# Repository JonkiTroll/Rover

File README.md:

# Rover
Implementation of a rc tank. Based on rctestflight's design.

# Requirements
Python 3.8 on server and rover

pyttsx3 python library for RoverTTS.py. For Ubuntu linux, libespeak1 needs to be installed manually (sudo apt install libespeak1).

OpenCv2 for Video_server.py. 

# Utilities
GPS 	GY-NEO6MV2

IMU	Icm20948 (Pid controller)

Camera (Servo)  logitech webcam

Speakers

Temp, gas, barometer, humidity https://www.bosch-sensortec.com/products/environmental-sensors/gas-sensors/bme688/

Neopixels

Battery management (Fuel gauge) https://www.ti.com/product/BQ34110#product-details##description

expansion headers (Servos, analog pins)

Hall Effect sensors x2 (3390Q)

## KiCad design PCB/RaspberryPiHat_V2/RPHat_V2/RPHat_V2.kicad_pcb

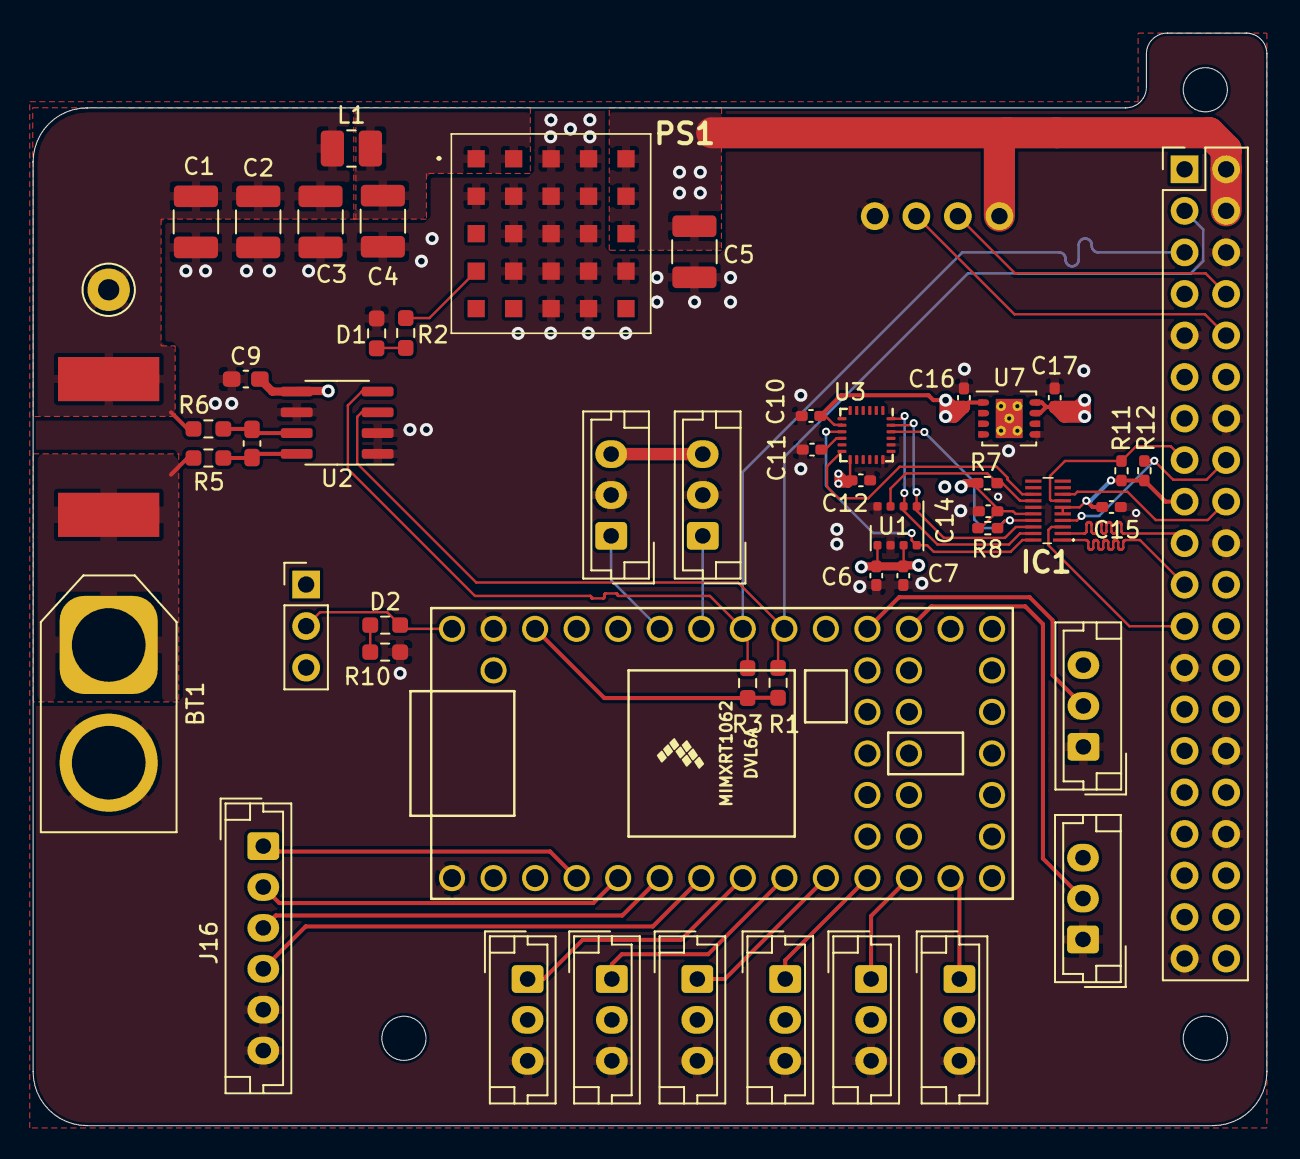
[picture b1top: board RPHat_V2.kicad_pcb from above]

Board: 4 copper layers, 75.4 x 66.8 mm, 53 parts (0 on the bottom side), 44 nets.

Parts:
BT1: Battery; AMASS_XT60-M_1x02_P7.20mm_Vertical
C1, C2, C3, C4, C5: 10uF; C_1210_3225Metric_Pad1.33x2.70mm_HandSolder
C6, C7, C10, C11, C12, C14, C15: 100nF; C_0402_1005Metric_Pad0.74x0.62mm_HandSolder
C8: DNC; C_0603_1608Metric_Pad1.08x0.95mm_HandSolder
C9: 100nF; C_0603_1608Metric_Pad1.08x0.95mm_HandSolder
C16: 4,7uF; C_0402_1005Metric_Pad0.74x0.62mm_HandSolder
C17: 1uF; C_0402_1005Metric_Pad0.74x0.62mm_HandSolder
D1, D2: LED; R_0603_1608Metric_Pad0.98x0.95mm_HandSolder
IC1: TXB0108DQSR
J1: Raspberry_Pi_2_3; PinHeader_2x20_P2.54mm_Vertical
J2: Hall effect connector Right; JST_EH_B3B-EH-A_1x03_P2.50mm_Vertical
J3: Halleffect Connector Left; JST_EH_B3B-EH-A_1x03_P2.50mm_Vertical
J5, J6, J7, J8, J11, J12, J13, J14: Conn_01x03; JST_EH_B3B-EH-A_1x03_P2.50mm_Vertical
J15: Conn_01x01; Pin_D1.3mm_L11.0mm
J16: Conn_01x06; JST_EH_B6B-EH-A_1x06_P2.50mm_Vertical
L1: 2.2uH; L_1008_2520Metric_Pad1.43x2.20mm_HandSolder
PS1: RPMB5.0-3.0; RPMB5030
R1, R3: TBU; R_0603_1608Metric_Pad0.98x0.95mm_HandSolder
R2: 1k; R_0603_1608Metric_Pad0.98x0.95mm_HandSolder
R4: 0.05; CSS2H-3920
R5, R6: 0; R_0603_1608Metric_Pad0.98x0.95mm_HandSolder
R7, R8, R11, R12: 100k; R_0402_1005Metric_Pad0.72x0.64mm_HandSolder
R10: 4.7k; R_0603_1608Metric_Pad0.98x0.95mm_HandSolder
SW1: SW_DPDT_x2; PinHeader_1x03_P2.54mm_Vertical
U1: BME680; Bosch_LGA-8_3x3mm_P0.8mm_ClockwisePinNumbering
U2: INA219AxD; SOIC-8_3.9x4.9mm_P1.27mm
U3: ICM-20948; InvenSense_QFN-24_3x3mm_P0.4mm
U4: GY-NEO6MV2
U6: Teensy4.0; Teensy40
U7: TPS78418QWDRBRQ1; Texas_S-PVSON-N8_ThermalVias

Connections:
+1V8: C6.1, C7.1, C10.1, C12.1, C14.1, C16.1, IC1.16, R7.1, R8.1, U1.6, U1.8, U3.8, U3.13, U7.1
+3V3: C9.1, C15.1, C17.1, IC1.5, IC1.6, J1.1, J1.17, J2.3, J3.3, R1.1, R3.1, R11.1, R12.1, U2.5, U6.31, U7.7, U7.8
+5V: C5.1, J1.2, J1.4, J5.2, J6.2, J7.2, J8.2, J11.3, J12.3, J13.2, J14.2, PS1.A5, PS1.B5, PS1.C5, SW1.1, U4.4
+BATT: BT1.1, R4.2, R5.1
BME_CS_18: IC1.14, R7.2, U1.2
BME_CS_33: IC1.7, J1.15, R11.2
GNDREF: BT1.2, C1.2, C2.2, C3.2, C4.2, C5.2, C6.2, C7.2, C9.2, C10.2, C11.2, C12.2, C14.2, C15.2, C16.2, C17.2, D1.1, IC1.15, J1.6, J1.9, J1.14, J1.20, J1.25, J1.30, J1.34, J1.39, J2.2, J3.2, J5.3, J6.3, J7.3, J8.3, J11.1, J12.1, J13.3, J14.3, J16.5, J16.6, PS1.A3, PS1.A4, PS1.B1, PS1.B2, PS1.B3, PS1.B4, PS1.C2, PS1.C3, PS1.C4, PS1.D2, PS1.D3, PS1.D4, PS1.D5, PS1.E3, PS1.E4, R10.2, U1.1, U1.7, U2.1, U2.2, U2.6, U3.18, U3.20, U4.1, U6.1, U6.32, U7.5, U7.9
GPS_RX: J1.8, U4.3
GPS_TX: J1.10, U4.2
HE_L_OUTPUT: J3.1, U6.28
HE_R_OUTPUT: J2.1, U6.27
IMU_CS_18: IC1.17, R8.2, U3.22
IMU_CS_33: IC1.4, J1.16, R12.2
IMU_INT_18: IC1.13, U3.12
IMU_INT_33: IC1.8, J1.18
Neopixels_1: J11.2, U6.22
Neopixels_2: J12.2, U6.23
unnamed: C4.1, L1.2, PS1.A1, PS1.A2
unnamed: C8.1, R5.2, U2.8
unnamed: C8.2, R6.2, U2.7
unnamed: C11.1, U3.10
unnamed: D1.2, R2.2
unnamed: D2.1, R10.1
unnamed: D2.2, SW1.2, U6.33
unnamed: PS1.D1, R2.1
PWM_Left_1: J16.2, U6.5
PWM_Left_2: J16.4, U6.7
PWM_Right_1: J16.1, U6.4
PWM_Right_2: J16.3, U6.6
PWMservo_1: J5.1, U6.8
PWMservo_2: J6.1, U6.9
PWMservo_3: J7.1, U6.10
PWMservo_4: J8.1, U6.11
PWMservo_5: J13.1, U6.12
PWMservo_6: J14.1, U6.13
SCL: J1.5, R3.2, U2.4, U6.26
SDA: J1.3, R1.2, U2.3, U6.25
SPI_CLK_18: IC1.18, U1.4, U3.23
SPI_CLK_33: IC1.3, J1.23
SPI_MISO_18: IC1.20, U1.5, U3.9
SPI_MISO_33: IC1.1, J1.21
SPI_MOSI_18: IC1.19, U1.3, U3.24
SPI_MOSI_33: IC1.2, J1.19
VCC: C1.1, C2.1, C3.1, J15.1, L1.1, R4.1, R6.1

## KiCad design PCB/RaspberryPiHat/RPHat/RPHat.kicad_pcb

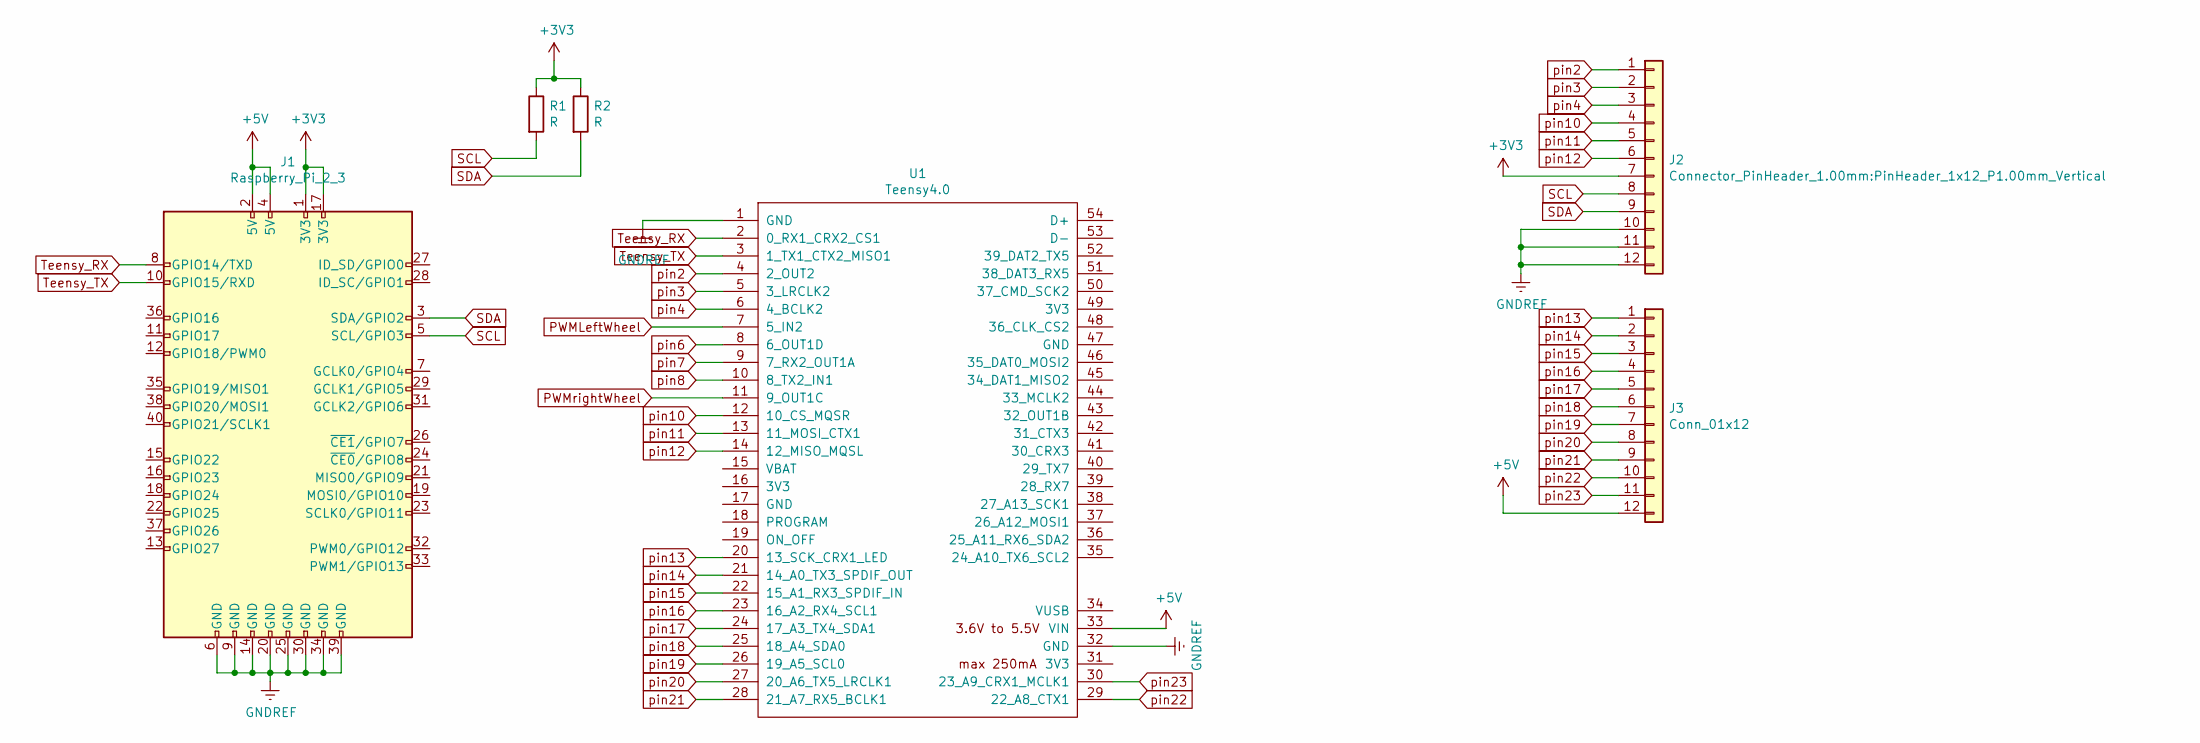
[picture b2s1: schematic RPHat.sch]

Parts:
J1: Raspberry_Pi_2_3; PinSocket_2x20_P2.54mm_Vertical
J2: Connector_PinHeader_1.00mm:PinHeader_1x12_P1.00mm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; PinHeader_1x12_P2.54mm_Vertical
J3: Conn_01x12; PinHeader_1x12_P2.54mm_Vertical
R1, R2: R; R_Box_L13.0mm_W4.0mm_P9.00mm
U1: Teensy4.0; Teensy40

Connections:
+3V3: J1.1 (3V3), J1.17 (3V3), J2.7, R1.1, R2.1
+5V: J1.2 (5V), J1.4 (5V), J3.12, U1.33 (VIN)
GNDREF: J1.6 (GND), J1.9 (GND), J1.14 (GND), J1.20 (GND), J1.25 (GND), J1.30 (GND), J1.34 (GND), J1.39 (GND), J2.10, J2.11, J2.12, U1.1 (GND), U1.32 (GND)
PWMLeftWheel: U1.7 (5_IN2)
PWMrightWheel: U1.11 (9_OUT1C)
SCL: J1.5 (SCL/GPIO3), J2.8, R1.2
SDA: J1.3 (SDA/GPIO2), J2.9, R2.2
Teensy_RX: J1.8 (GPIO14/TXD), U1.2 (0_RX1_CRX2_CS1)
Teensy_TX: J1.10 (GPIO15/RXD), U1.3 (1_TX1_CTX2_MISO1)
pin2: J2.1, U1.4 (2_OUT2)
pin3: J2.2, U1.5 (3_LRCLK2)
pin4: J2.3, U1.6 (4_BCLK2)
pin6: U1.8 (6_OUT1D)
pin7: U1.9 (7_RX2_OUT1A)
pin8: U1.10 (8_TX2_IN1)
pin10: J2.4, U1.12 (10_CS_MQSR)
pin11: J2.5, U1.13 (11_MOSI_CTX1)
pin12: J2.6, U1.14 (12_MISO_MQSL)
pin13: J3.1, U1.20 (13_SCK_CRX1_LED)
pin14: J3.2, U1.21 (14_A0_TX3_SPDIF_OUT)
pin15: J3.3, U1.22 (15_A1_RX3_SPDIF_IN)
pin16: J3.4, U1.23 (16_A2_RX4_SCL1)
pin17: J3.5, U1.24 (17_A3_TX4_SDA1)
pin18: J3.6, U1.25 (18_A4_SDA0)
pin19: J3.7, U1.26 (19_A5_SCL0)
pin20: J3.8, U1.27 (20_A6_TX5_LRCLK1)
pin21: J3.9, U1.28 (21_A7_RX5_BCLK1)
pin22: J3.10, U1.29 (22_A8_CTX1)
pin23: J3.11, U1.30 (23_A9_CRX1_MCLK1)

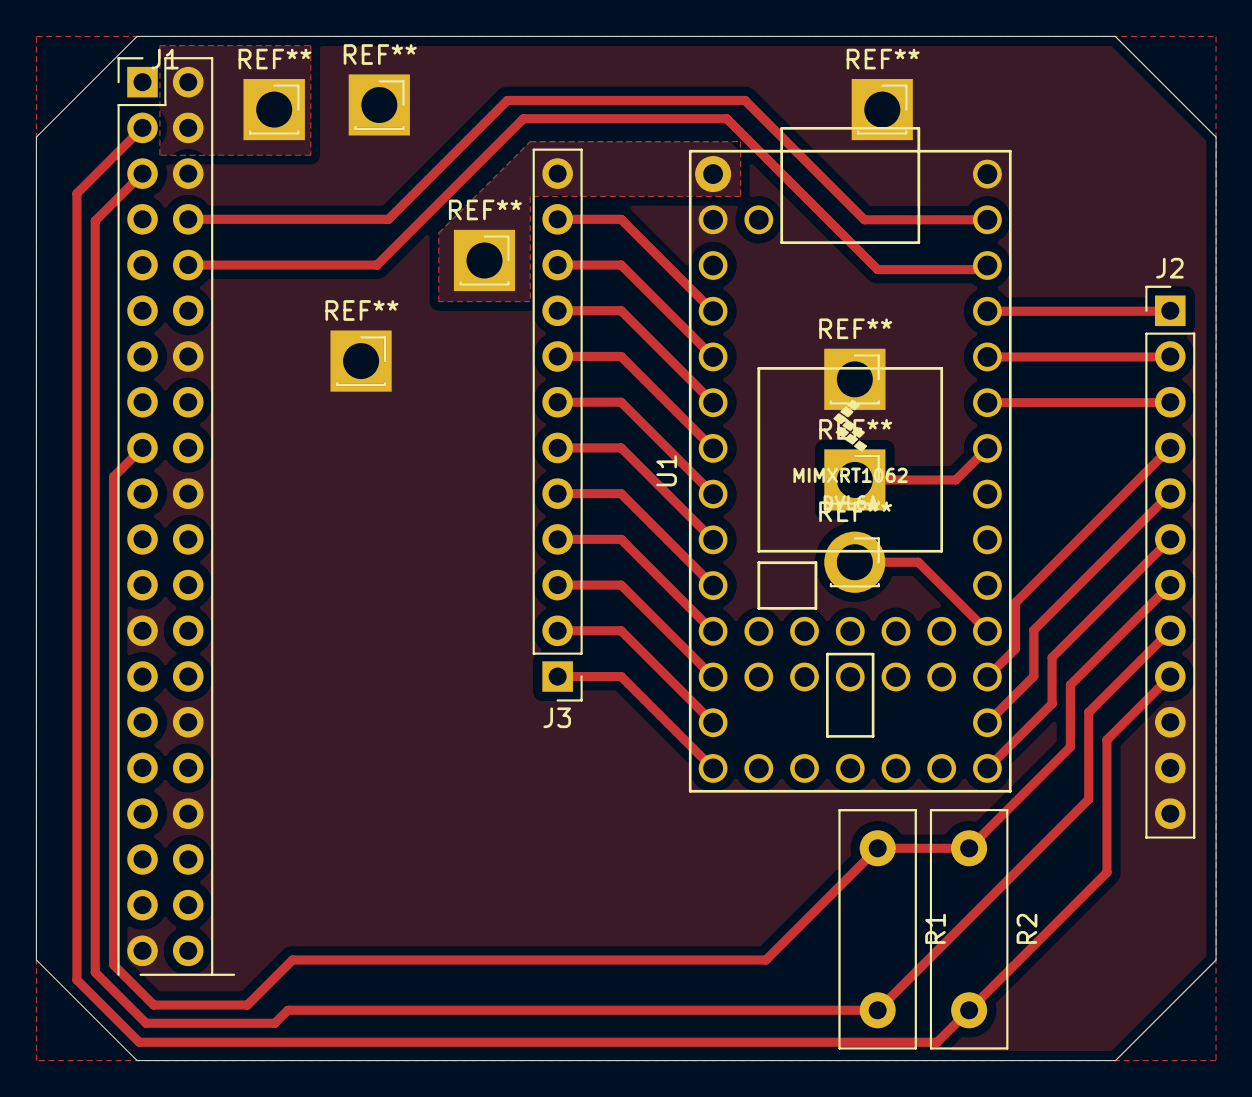
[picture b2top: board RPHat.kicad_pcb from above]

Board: 2 copper layers, 65.5 x 56.9 mm, 6 parts (0 on the bottom side), 24 nets.

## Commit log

2021-01-31 Added gitignore
2021-01-31 Added gitignore file for the build files
2021-01-31 fixed gitignore
2021-01-31 Create server.py
    wooooooooooooooooooooooow we have a server
2021-01-31 More fixes cuz Im a retard
2021-01-31 Moved python script to its own folder
2021-02-02 Moved the udp server to the correct location
    hell yea i did it and there is nothing you can do about it
2021-02-02 Moved things around and made a tts script
    now the rover will be able to tell ppl to go F*** them self
2021-02-03 organized the project. Started porting the code over to C++ due to better threading support.
2021-02-03 added a video streaming prodocall with cv2
    it streams and it buggs
    maybe we will use a video call thing instead but this is is how it is now
2021-02-04 Ported the code over to C++.
2021-02-04 Added TODOs to the code
2021-02-04 Changed to support C++
2021-02-05 setup server to only serve controller, rover comunications
2021-02-08 Woooooooooooooooow we have some sort of a viideo stream going on
2021-02-09 Created a multithreaded controller script. Also reorganized the project.
2021-02-09 Delete Code/Raspberry directory
    Directory is useless now.
2021-02-09 Why am I bad at github
2021-05-01 started reworking the code
2021-05-01 Why cant I just learn github
2021-05-12 Working on the PCB
2021-05-12 Configured pinout for logic converter
2021-05-13 Started routing for the BMS
2021-05-15 Continued routing the pcb. Added current sensing sensor
2021-05-15 Schematic clean-up
2021-05-17 Continued updating the roverclient code
2021-05-19 Started routing PCB
2021-05-22 Added footprints to all componetns
2021-05-25 started pcb routing
2021-05-26 Continued working on the pcb
2021-05-29 Never gonna give you up
2021-05-30 working on pcb Ja!
2021-06-10 pcb update
2021-06-11 Work, work, work
2021-06-12 PCB done. only a few grounding vias left to add
2021-06-14 retraced as well as added ground vias
2021-06-19 Commit update
2021-07-22 Fixed linking issue and finished pcb
2022-06-17 Did some cleanup
2022-06-17 moving to a linux enviorment
2022-06-19 figureing out how the webinterface is going to work
2022-09-19 Update main.cpp
    Removed IP address
2022-09-19 Update udpClientController.cpp
    Removed IP address
